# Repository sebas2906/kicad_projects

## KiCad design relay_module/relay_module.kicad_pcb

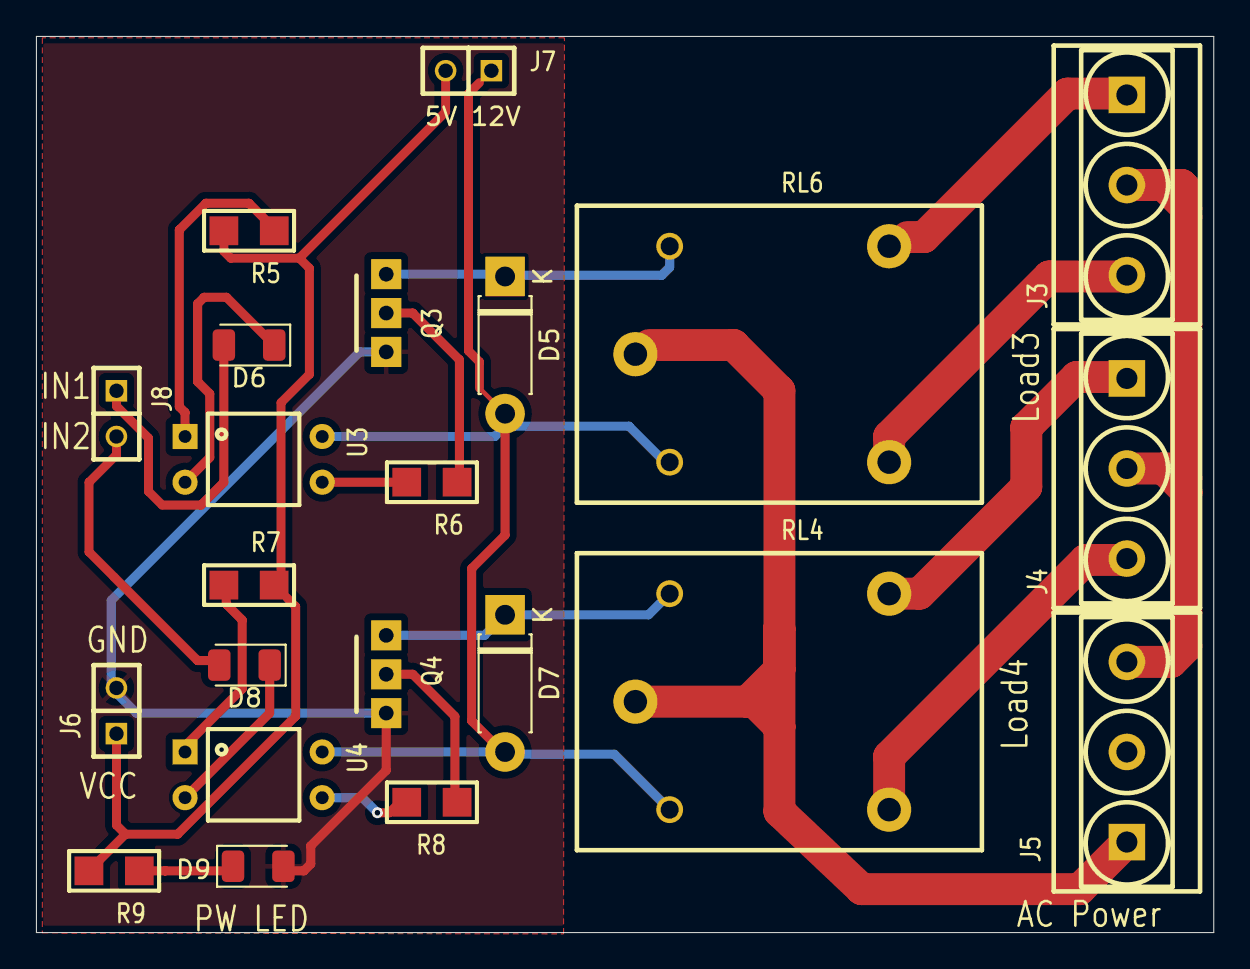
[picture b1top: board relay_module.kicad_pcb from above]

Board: 2 copper layers, 65.4 x 49.8 mm, 22 parts (0 on the bottom side), 22 nets.

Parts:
D5, D7: 1N4007; D_DO-41_SOD81_P7.62mm_Horizontal
D6, D8, D9: SMD LED; LED_1206_3216Metric
J3: Loa3; H3-5.0-15.5X8.0MMxx96xvaluexx96xAC In
J4: Load4; H3-5.0-15.5X8.0MMxx96xvaluexx96xAC In
J5: ExternalPower; H3-5.0-15.5X8.0MMxx96xvaluexx96xAC In
J6: pwr; M1X2xx96xvaluexx96xPW In
J7: Vcc; M1X2xx96xvaluexx96xPW In
J8: input; M1X2xx96xvaluexx96xPW In
Q3, Q4: BC547A; TO92-INLINExx96xvaluexx96xBC547B
R5, R6, R7, R8, R9: 1k; R1206xx96xvaluexx96x1k
RL4, RL6: 12v RLY; Omron_G5LE_SPDT_Relayxx96xvaluexx96x12v
U3, U4: PCF817; DIP4xx96xvaluexx96xPCF817

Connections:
12V: D5.2 (K), D7.2 (K), J7.1, RL4.2 (COIL2), RL6.2 (COIL2), U3.4, U4.4
+5V: J6.1, J7.2, R5.2, R7.2, R9.2
GND: D9.2 (CATHODE), J6.2, Q3.3 (E), Q4.3 (E)
N: J3.2, J4.2, J5.3
unnamed: D5.1 (A), Q3.1 (C), RL6.5 (COIL1)
unnamed: D6.1 (ANODE), U3.2
unnamed: D7.1 (A), Q4.1 (C), RL4.5 (COIL1)
unnamed: D8.1 (ANODE), U4.2
unnamed: D9.1 (ANODE), R9.1
unnamed: J3.1, RL6.4 (NC)
unnamed: J3.3, RL6.3 (NO)
unnamed: J4.1, RL4.4 (NC)
unnamed: J4.3, RL4.3 (NO)
unnamed: Q3.2 (B), R6.1
unnamed: Q4.2 (B), R8.1
unnamed: R5.1, U3.1
unnamed: R6.2, U3.3
unnamed: R7.1, U4.1
unnamed: R8.2, U4.3
P: J5.1, RL4.1 (MAIN), RL6.1 (MAIN)
rly3: D6.2 (CATHODE), J8.1
rly4: D8.2 (CATHODE), J8.2

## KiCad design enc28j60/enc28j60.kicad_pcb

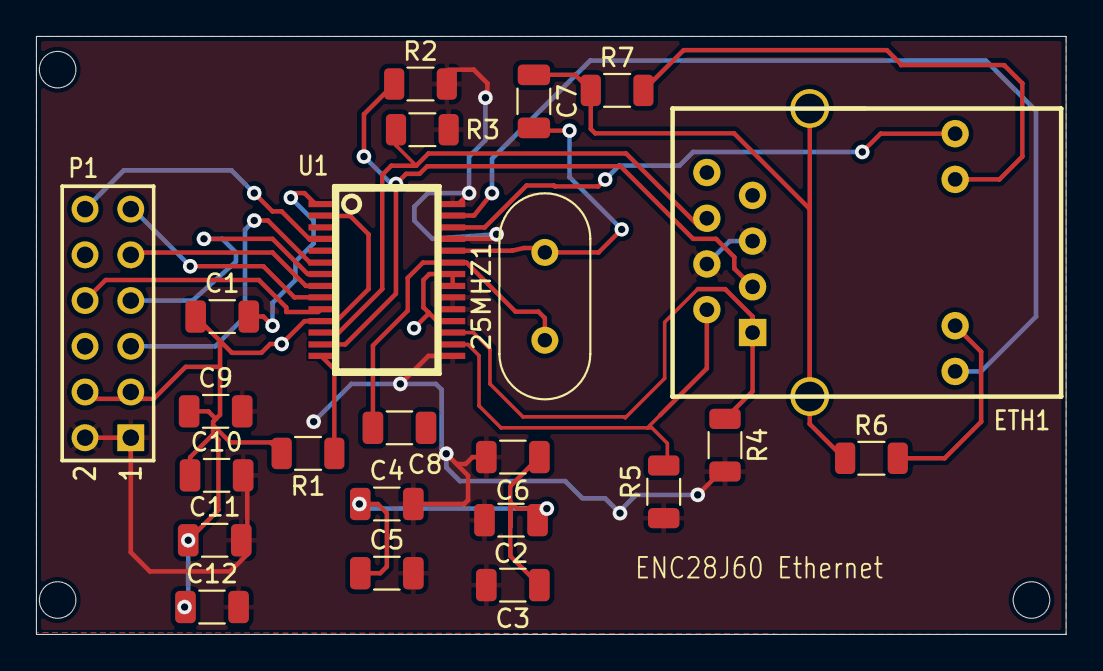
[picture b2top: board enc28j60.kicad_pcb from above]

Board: 2 copper layers, 57.2 x 33.2 mm, 23 parts (0 on the bottom side), 20 nets.

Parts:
25MHZ1: XTALfast; Crystal_HC49-4H_Vertical
C1, C2, C3, C4, C5, C6, C9, C10, C11, C12: 1u; C_1206_3216Metric
C7, C8: 20p; C_1206_3216Metric
ETH1: CON-RJ45-F; HR911105A
P1: HDR2X6
R1, R2, R3, R4, R5, R6, R7: 1k; R_1206_3216Metric
U1: ENC28J60; SSOP28DB

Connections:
3.3V: C2.2, C3.2, C4.2, C5.2, C6.2, C9.2, C10.2, C11.2, C12.2, ETH1.4, ETH1.5, P1.1, P1.2, R2.2, R3.2, R4.2, R5.2, U1.15 (VDDTX), U1.19 (VDDRX), U1.20 (VDDPLL), U1.25 (VDDOSC), U1.28 (VDD)
/CS: P1.11, U1.9 (CS)
/INT: P1.12, U1.4 (INT)
/LEDA: ETH1.9, U1.27 (LEDA)
/LEDB: ETH1.12, U1.26 (LEDB)
/MISO: P1.5, U1.6 (SO)
/MOSI: P1.7, U1.7 (SI)
/RESET: P1.8, U1.10 (RESET)
/SCK: P1.9, U1.8 (SCK)
/TPIN+: ETH1.3, R2.1, U1.13 (TPIN+)
/TPIN-: ETH1.6, R3.1, U1.12 (TPIN-)
/TPOUT+: ETH1.1, R4.1, U1.17 (TPOUT+)
/TPOUT-: ETH1.2, R5.1, U1.16 (TPOUT-)
GND: C1.1, C2.1, C3.1, C4.1, C5.1, C6.1, C7.1, C9.1, C10.1, C11.1, C12.1, ETH1.13, ETH1.14, P1.3, P1.4, R1.2, R6.1, R7.1, U1.2 (VSS), U1.11 (VSSRX), U1.18 (VSSTX), U1.21 (VSSPLL), U1.22 (VSSOSC)
unnamed: 25MHZ1.1 (OSC1), C8.2, U1.23 (OSC1)
unnamed: 25MHZ1.2 (OSC2), C7.2, U1.24 (OSC2)
unnamed: C1.2, U1.1 (VCAP)
unnamed: ETH1.10, R6.2
unnamed: ETH1.11, R7.2
unnamed: R1.1, U1.14 (RBIAS)

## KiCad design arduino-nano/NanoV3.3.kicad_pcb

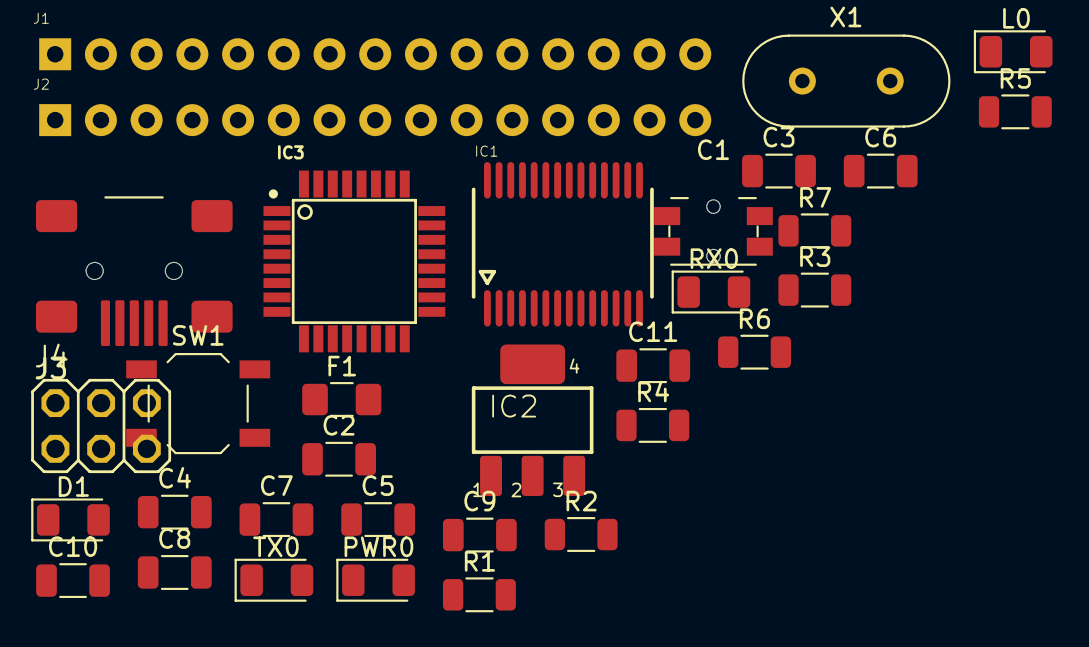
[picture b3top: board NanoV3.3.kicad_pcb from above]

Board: 2 copper layers, 36 parts (0 on the bottom side), 43 nets, no tracks yet.

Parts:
C1: 100nF; Panasonic_EVQPUM_EVQPUD
C2, C5: 4,7uF_16V; C_1206_3216Metric
C3, C7, C8: 1uF; C_1206_3216Metric
C4, C6, C9: 100nF; C_1206_3216Metric
C10, C11: 22pF; C_1206_3216Metric
D1: SS1P3L; D_1206_3216Metric
D+0: DNP; TP-1.00MM
D-0: DNP; TP-1.00MM
F1: MFFSMF050; Fuse_1206_3216Metric_Pad1.42x1.75mm_HandSolder
FRAME1: DNP; FRAME
IC1: FT232RL; SSOP28
IC2: LM1117IMPX-5.0; LINEAR_SOT223
IC3: 328P-MUR; QFP80P900X900X120-32N
J1, J2: XXXX_STRIPNANO; HEAD15-NOSS
J3: 0219_14850; USB-MINI-B_2
J4: 0114_PH254-203DF118A00V; 2X03
L0: Yellow; LED_1206_3216Metric
PWR0: Green; LED_1206_3216Metric
R1: 1k; R_1206_3216Metric
R2, R3, R4, R5, R6, R7: 1K; R_1206_3216Metric
RX0: Red; LED_1206_3216Metric
SW1: RESET; SW_SPST_TL3342
TX0: Green; LED_1206_3216Metric
X1: 16MHz; Crystal_HC49-4H_Vertical

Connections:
3V3: C6.2, IC1.17 (3V3OUT), J2.14
+5V: C3.1, C5.1 (+), C7.1, C8.1, D1.1 (K), IC1.4 (VCCIO), IC1.20 (VCC), IC2.2 (OUT@1), IC2.4 (OUT), IC3.4 (VCC@1), IC3.6 (VCC@2), IC3.18 (AVCC), J2.4, J4.2, R1.1, R7.1, RX0.1 (A), TX0.1 (A)
/A0: IC3.23 (PC0(ADC0)), J2.12
/A1: IC3.24 (PC1(ADC1)), J2.11
/A2: IC3.25 (PC2(ADC2)), J2.10
/A3: IC3.26 (PC3(ADC3)), J2.9
/A4: IC3.27 (PC4(ADC4/SDA)), J2.8
/A5: IC3.28 (PC5(ADC5/SCL)), J2.7
/A6: IC3.19 (ADC6), J2.6
/A7: IC3.22 (ADC7), J2.5
/AREF: C1.1, IC3.20 (AREF), J2.13
/D0/RX: IC3.30 (PD0(RXD)), J1.2, R3.1
/D1/TX: IC3.31 (PD1(TXD)), J1.1, R2.1
/D2: IC3.32 (PD2(INT0)), J1.5
/D3: IC3.1 (PD3(INT1)), J1.6
/D4: IC3.2 (PD4(XCK/T0)), J1.7
/D5: IC3.9 (PD5(T1)), J1.8
/D6: IC3.10 (PD6(AIN0)), J1.9
/D7: IC3.11 (PD7(AIN1)), J1.10
/D8: IC3.12 (PB0(ICP)), J1.11
/D9: IC3.13 (PB1(OC1A)), J1.12
/D10: IC3.14 (PB2(SS/OC1B)), J1.13
/D11/MOSI: IC3.15 (PB3(MOSI/OC2)), J1.14, J4.4
/D12/MISO: IC3.16 (PB4(MISO)), J1.15, J4.1
/D13/SCK: IC3.17 (PB5(SCK)), J2.15, J4.3, R4.2
/RESET: C4.1, IC3.29 (PC6(/RESET)), J1.3, J2.3, J4.5, R1.2, SW1.2
/RX: IC1.1 (TXD), R3.2
/TX: IC1.5 (RXD), R2.2
COM: C1.2, C2.2 (-), C3.2, C5.2 (-), C6.1, C7.2, C8.2, C9.2, C10.1, C11.1, IC1.7 (GND1), IC1.18 (GND2), IC1.21 (GND3), IC1.25 (AGND), IC1.26 (TEST), IC2.1 (GND/ADJ), IC3.3 (GND@1), IC3.5 (GND@2), IC3.21 (AGND), J1.4, J2.2, J3.1 (GND), J3.6 (SH1), J3.7 (SH2), J3.8 (SH3), J3.9 (SH4), J4.6, L0.2 (C), PWR0.2 (C), SW1.1
unnamed: C4.2, IC1.2 (DTR#)
unnamed: D+0.X, IC1.15 (USBDP), J3.3 (D+)
unnamed: D-0.X, IC1.16 (USBDM), J3.4 (D-)
unnamed: F1.2, J3.5 (VBUS)
unnamed: IC1.22 (CBUS1), R5.1
unnamed: IC1.23 (CBUS0), R6.1
unnamed: C11.2, IC3.7 (PB6(XTAL1/TOSC1)), X1.1
unnamed: C10.2, IC3.8 (PB7(XTAL2/TOSC2)), X1.2
unnamed: L0.1 (A), R4.1
unnamed: PWR0.1 (A), R7.2
unnamed: R5.2, TX0.2 (C)
unnamed: R6.2, RX0.2 (C)
VIN: IC2.3 (IN), J2.1
VUSB: C2.1 (+), C9.1, D1.2 (A), F1.1

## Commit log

2022-10-09 Finalizado primera entrega proyecto de alarmas_comunitarias
